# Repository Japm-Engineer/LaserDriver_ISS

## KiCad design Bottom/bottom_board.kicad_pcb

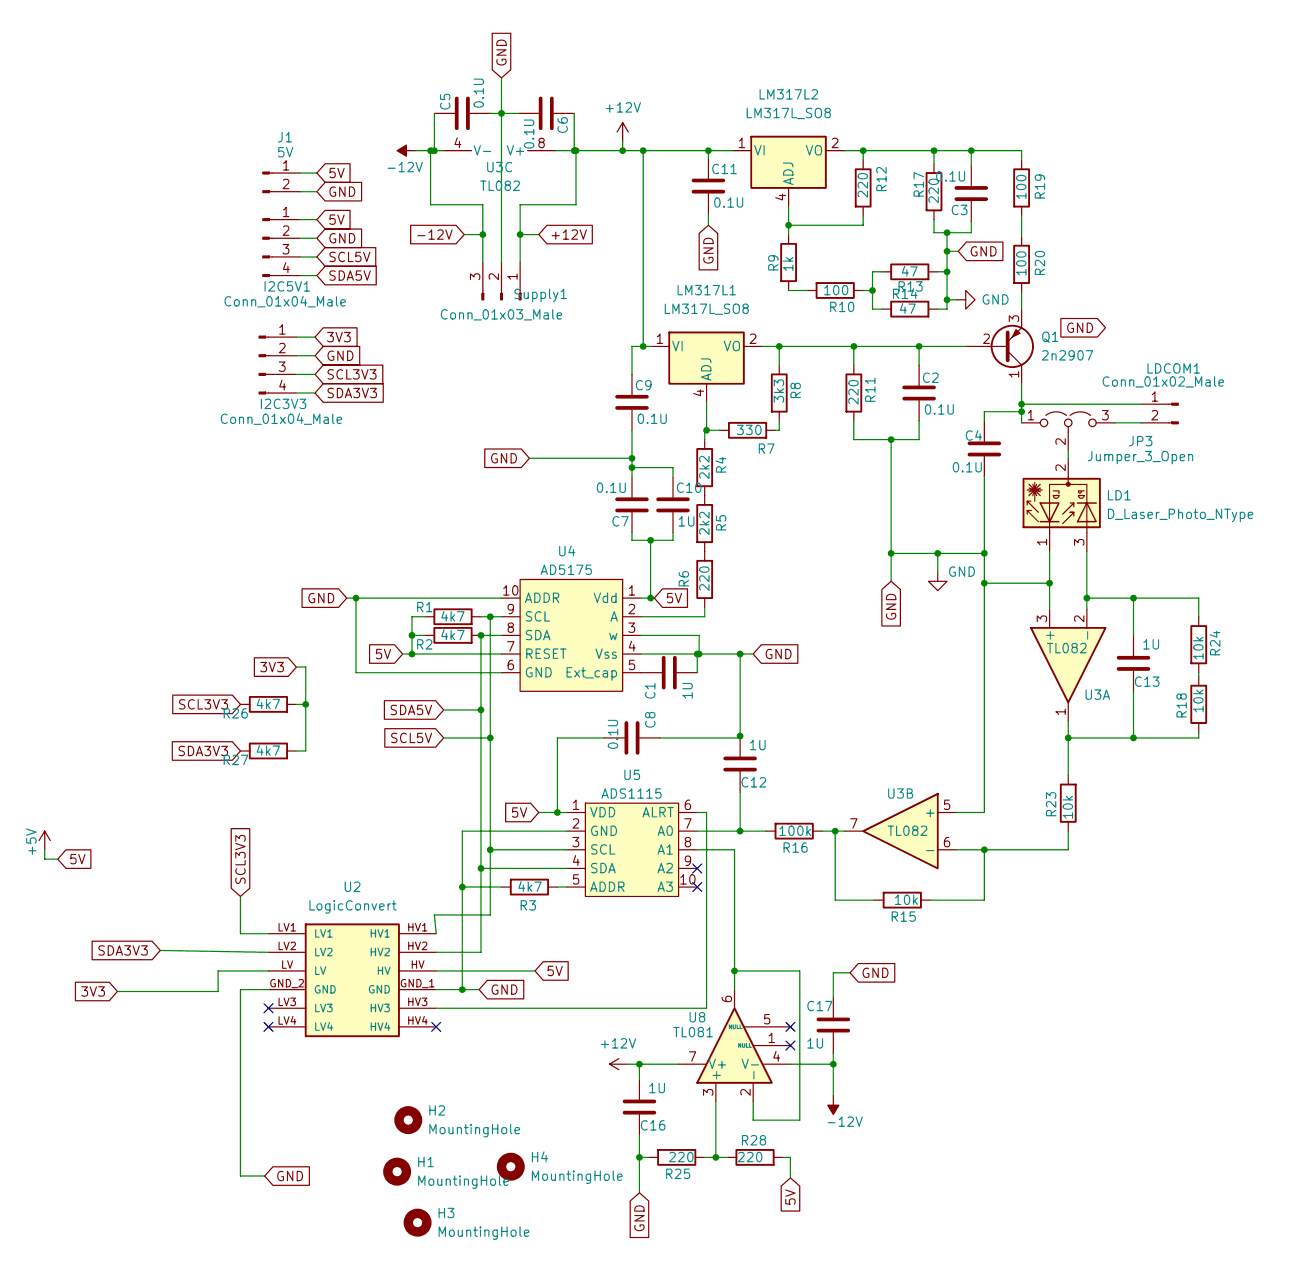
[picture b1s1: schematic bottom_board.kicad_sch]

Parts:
C1, C10, C12, C13, C16, C17: 1U; C_0805_2012Metric_Pad1.18x1.45mm_HandSolder
C2, C3, C4, C5, C6, C7, C8, C9, C11: 0.1U; C_0805_2012Metric_Pad1.18x1.45mm_HandSolder
H1, H2, H3, H4: MountingHole; MountingHole_3.2mm_M3
I2C3V3, I2C5V1: Conn_01x04_Male; JST_XA_B04B-XASK-1_1x04_P2.50mm_Vertical
J1: 5V; JST_EH_B2B-EH-A_1x02_P2.50mm_Vertical
JP3: Jumper_3_Open; PinHeader_1x03_P2.54mm_Vertical
LD1: D_Laser_Photo_NType; JST_XH_B3B-XH-A_1x03_P2.50mm_Vertical
LDCOM1: Conn_01x02_Male; JST_EH_B2B-EH-A_1x02_P2.50mm_Vertical
LM317L1, LM317L2: LM317L_SO8; SO-8_3.9x4.9mm_P1.27mm
Q1: 2n2907; TO-92_Inline_Wide
R1, R2, R3, R26, R27: 4k7; R_1210_3225Metric_Pad1.30x2.65mm_HandSolder
R4, R5: 2k2; R_1210_3225Metric_Pad1.30x2.65mm_HandSolder
R6, R12, R25, R28: 220; R_1210_3225Metric_Pad1.30x2.65mm_HandSolder
R7: 330; R_1210_3225Metric_Pad1.30x2.65mm_HandSolder
R8: 3k3; R_1210_3225Metric_Pad1.30x2.65mm_HandSolder
R9: 1k; R_1210_3225Metric_Pad1.30x2.65mm_HandSolder
R10: 100; R_1210_3225Metric_Pad1.30x2.65mm_HandSolder
R11, R17: 220; R_Axial_DIN0614_L14.3mm_D5.7mm_P20.32mm_Horizontal
R13, R14: 47; R_1210_3225Metric_Pad1.30x2.65mm_HandSolder
R15, R18, R23, R24: 10k; R_1210_3225Metric_Pad1.30x2.65mm_HandSolder
R16: 100k; R_1210_3225Metric_Pad1.30x2.65mm_HandSolder
R19, R20: 100; R_Axial_DIN0614_L14.3mm_D5.7mm_P20.32mm_Horizontal
Supply1: Conn_01x03_Male; JST_XH_B3B-XH-A_1x03_P2.50mm_Vertical
U2: LogicConvert; CONV_BOB-12009; PARTREV 01
U3: TL082; SO-8_5.3x6.2mm_P1.27mm
U4: AD5175; MSOP-10_3x3mm_P0.5mm
U5: ADS1115
U8: TL081; DIP-8_W7.62mm

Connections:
3V3: I2C3V3.1, R26.2, R27.2, U2.LV
5V: C7.1, C8.2, C10.2, I2C5V1.1, J1.1, R1.1, R2.1, R28.2, U2.HV, U4.1 (Vdd), U4.7 (RESET), U5.1 (VDD)
+12V: C6.1, C9.1, C11.1, C16.2, LM317L1.1 (VI), LM317L2.1 (VI), Supply1.1, U3.8 (V+), U8.7 (V+)
-12V: C5.1, C17.2, Supply1.3, U3.4 (V-), U8.4 (V-)
GND: C1.2, C2.2, C3.1, C4.2, C5.2, C6.2, C7.2, C8.1, C9.2, C10.1, C11.2, C12.2, C16.1, C17.1, I2C3V3.2, I2C5V1.2, J1.2, LD1.1, R3.2, R11.2, R13.2, R14.2, R17.2, R25.2, Supply1.2, U2.GND_1 (GND), U2.GND_2 (GND), U3.3 (+), U3.5 (+), U4.3 (w), U4.4 (Vss), U4.6 (GND), U4.10 (ADDR), U5.2 (GND)
unnamed: C3.2, LM317L2.2 (VO), LM317L2.3 (VO), LM317L2.6 (VO), LM317L2.7 (VO), R12.1, R17.1, R19.1
unnamed: C13.1, R18.1, R23.2, U3.1
unnamed: C4.1, JP3.1 (A), LDCOM1.1, Q1.1 (C)
unnamed: JP3.3 (B), LDCOM1.2
unnamed: JP3.2 (C), LD1.2
unnamed: LM317L1.4 (ADJ), R4.1, R7.1
unnamed: LM317L2.4 (ADJ), R9.1, R12.2
unnamed: C2.1, LM317L1.2 (VO), LM317L1.3 (VO), LM317L1.6 (VO), LM317L1.7 (VO), Q1.2 (B), R8.1, R11.1
unnamed: Q1.3 (E), R20.2
unnamed: R4.2, R5.1
unnamed: R5.2, R6.2
unnamed: R7.2, R8.2
unnamed: R10.1, R13.1, R14.1
unnamed: R9.2, R10.2
unnamed: R15.2, R16.1, U3.7
unnamed: R18.2, R24.2
unnamed: R19.2, R20.1
unnamed: C13.2, LD1.3, R24.1, U3.2 (-)
unnamed: R15.1, R23.1, U3.6 (-)
unnamed: R6.1, U4.2 (A)
unnamed: C1.1, U4.5 (Ext_cap)
unnamed: C12.1, R16.2, U5.7 (A0)
unnamed: U5.8 (A1), U8.2 (-), U8.6
unnamed: R3.1, U5.5 (ADDR)
unnamed: U2.HV3, U5.6 (ALRT)
unnamed: R25.1, R28.1, U8.3 (+)
SCL3V3: I2C3V3.3, R26.1, U2.LV1
SCL5V: I2C5V1.3, R1.2, U2.HV1, U4.9 (SCL), U5.3 (SCL)
SDA3V3: I2C3V3.4, R27.1, U2.LV2
SDA5V: I2C5V1.4, R2.2, U2.HV2, U4.8 (SDA), U5.4 (SDA)

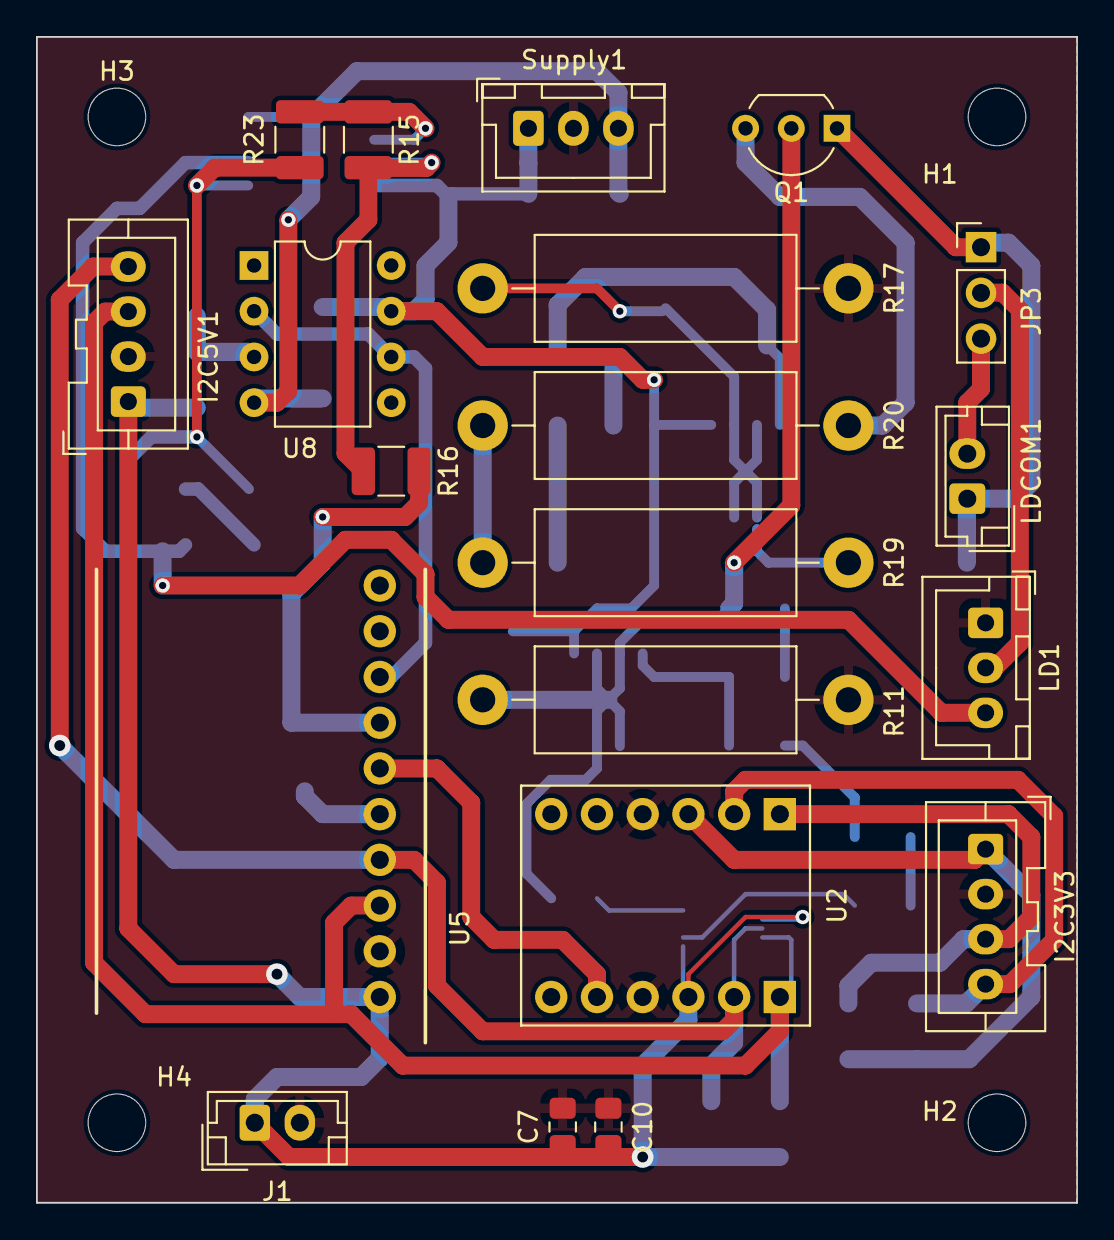
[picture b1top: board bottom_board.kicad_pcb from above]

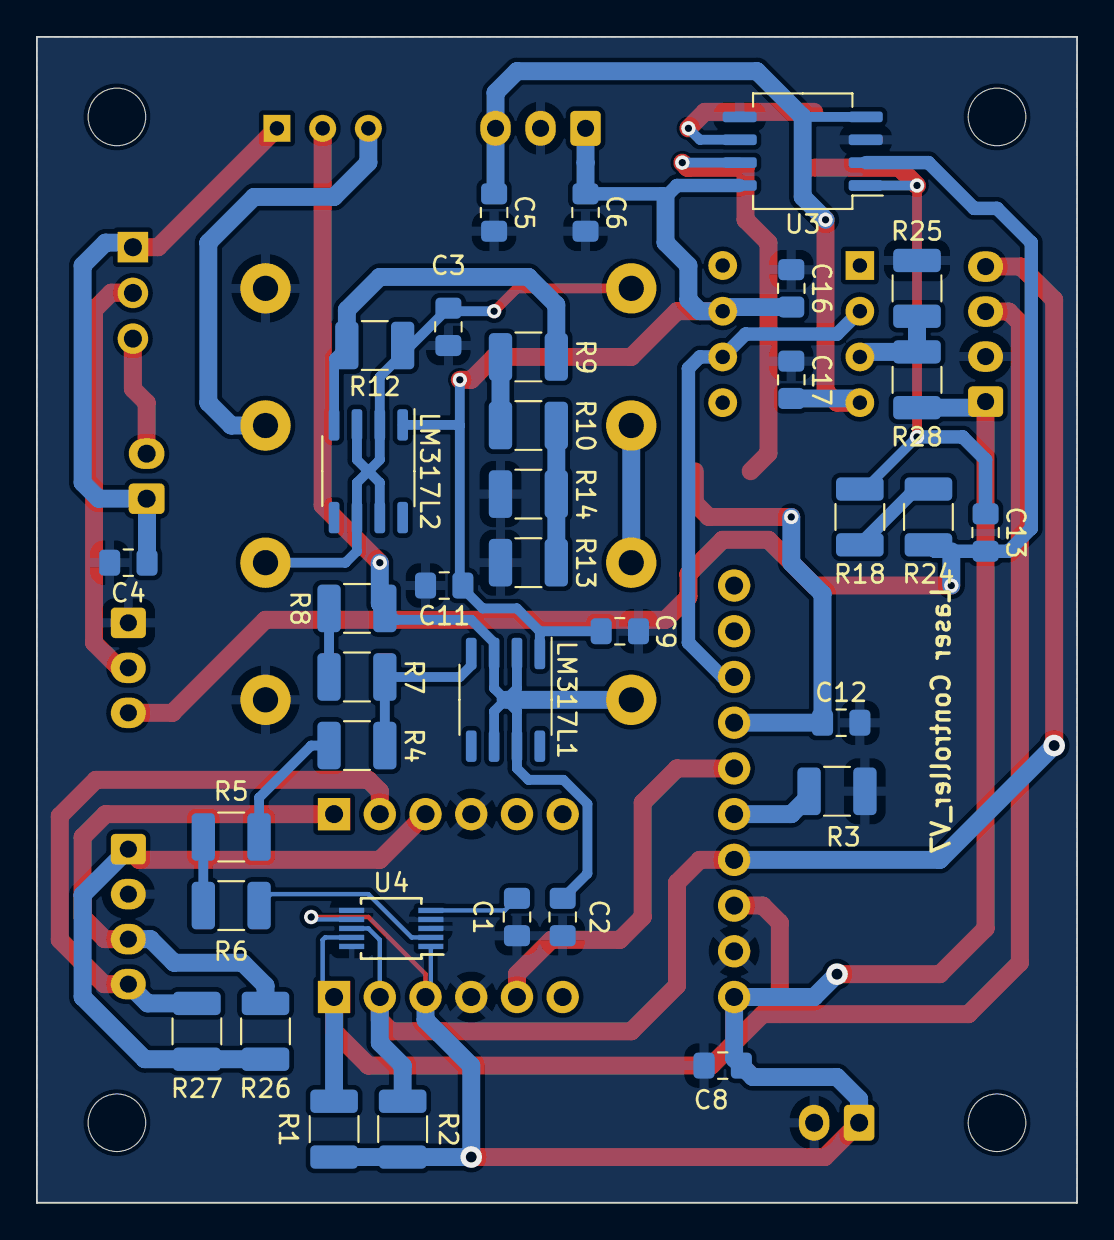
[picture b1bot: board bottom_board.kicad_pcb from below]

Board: 2 copper layers, 57.8 x 64.8 mm, 60 parts (36 on the bottom side), 35 nets.

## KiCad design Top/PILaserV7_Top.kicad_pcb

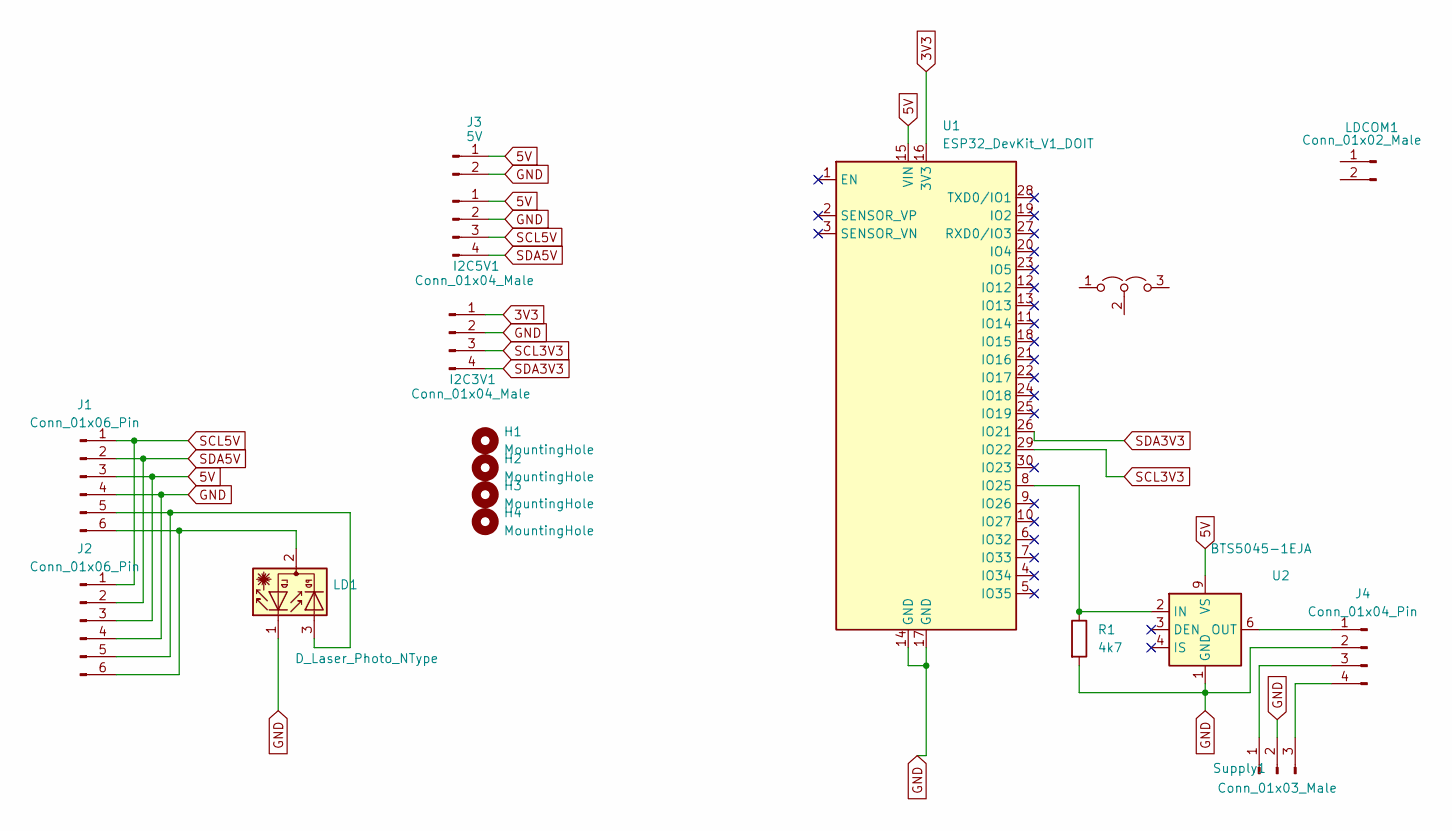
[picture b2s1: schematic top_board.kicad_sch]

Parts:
H1, H2, H3, H4: MountingHole; MountingHole_3.2mm_M3
I2C3V1, I2C5V1: Conn_01x04_Male; JST_XA_B04B-XASK-1_1x04_P2.50mm_Vertical
J1: Conn_01x06_Pin; PinHeader_1x06_P2.54mm_Vertical
J2: Conn_01x06_Pin; Molex_Pico-Lock_504050-0691_1x06-1MP_P1.50mm_Horizontal
J3: 5V; JST_EH_B2B-EH-A_1x02_P2.50mm_Vertical
J4: Conn_01x04_Pin; Molex_Pico-Lock_504050-0491_1x04-1MP_P1.50mm_Horizontal
JP1: Jumper_3_Open; PinHeader_1x03_P2.54mm_Vertical
LD1: D_Laser_Photo_NType; JST_XH_B3B-XH-A_1x03_P2.50mm_Vertical
LDCOM1: Conn_01x02_Male; JST_EH_B2B-EH-A_1x02_P2.50mm_Vertical
R1: 4k7; R_0805_2012Metric_Pad1.20x1.40mm_HandSolder
Supply1: Conn_01x03_Male; JST_XH_B3B-XH-A_1x03_P2.50mm_Vertical
U1: ESP32_DevKit_V1_DOIT; esp32_devkit_v1_doit
U2: BTS5045-1EJA; Infineon_PG-DSO-8-43

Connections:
3V3: I2C3V1.1, U1.16 (3V3)
5V: I2C5V1.1, J1.3, J2.3, J3.1, U1.15 (VIN), U2.9 (VS)
GND: I2C3V1.2, I2C5V1.2, J1.4, J2.4, J3.2, J4.2, LD1.1, R1.2, Supply1.2, U1.14 (GND), U1.17 (GND), U2.1 (GND)
unnamed: J1.5, J2.5, LD1.3
unnamed: J1.6, J2.6, LD1.2
unnamed: J4.1, U2.6 (OUT), U2.7 (OUT), U2.8 (OUT)
unnamed: J4.3, Supply1.1
unnamed: J4.4, Supply1.3
unnamed: R1.1, U1.8 (IO25), U2.2 (IN)
SCL3V3: I2C3V1.3, U1.29 (IO22)
SCL5V: I2C5V1.3, J1.1, J2.1
SDA3V3: I2C3V1.4, U1.26 (IO21)
SDA5V: I2C5V1.4, J1.2, J2.2

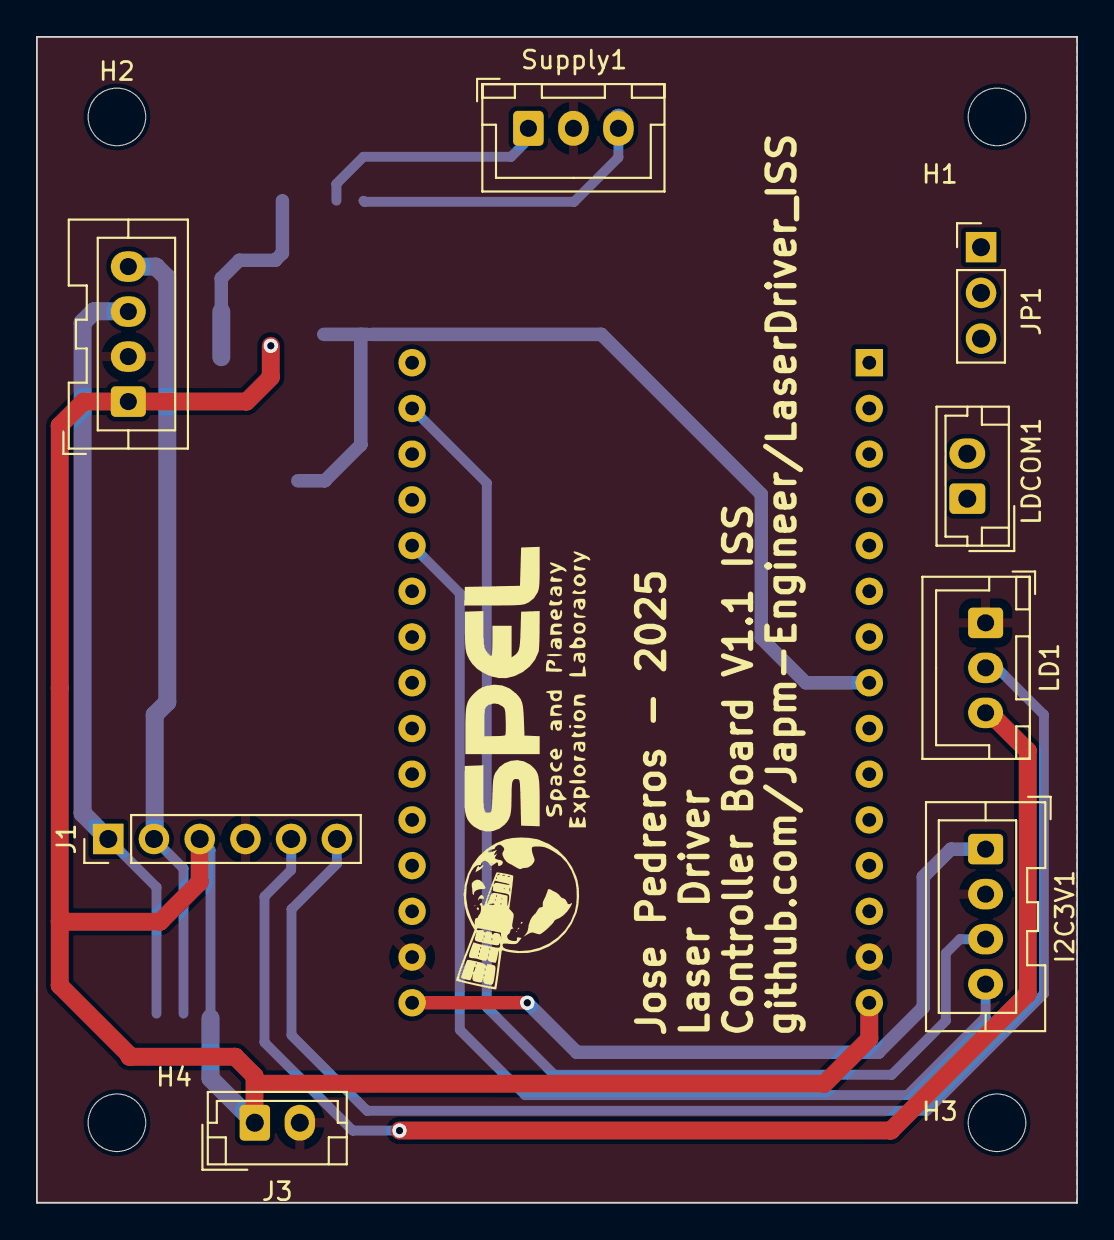
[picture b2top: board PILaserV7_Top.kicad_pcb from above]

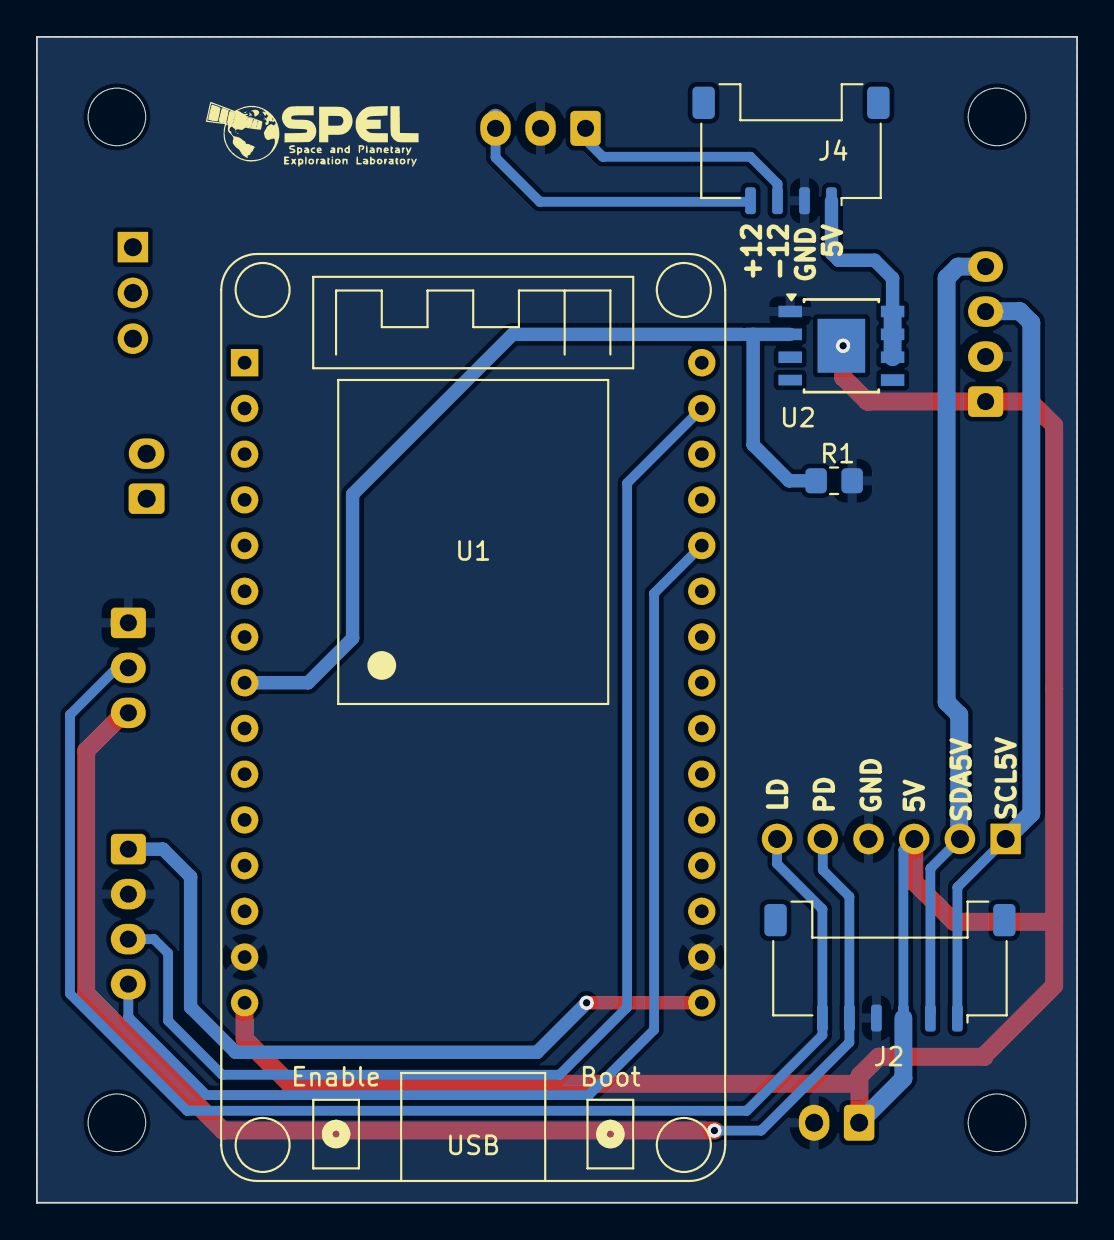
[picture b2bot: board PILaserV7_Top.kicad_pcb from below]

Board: 2 copper layers, 57.8 x 64.8 mm, 17 parts (5 on the bottom side), 13 nets.

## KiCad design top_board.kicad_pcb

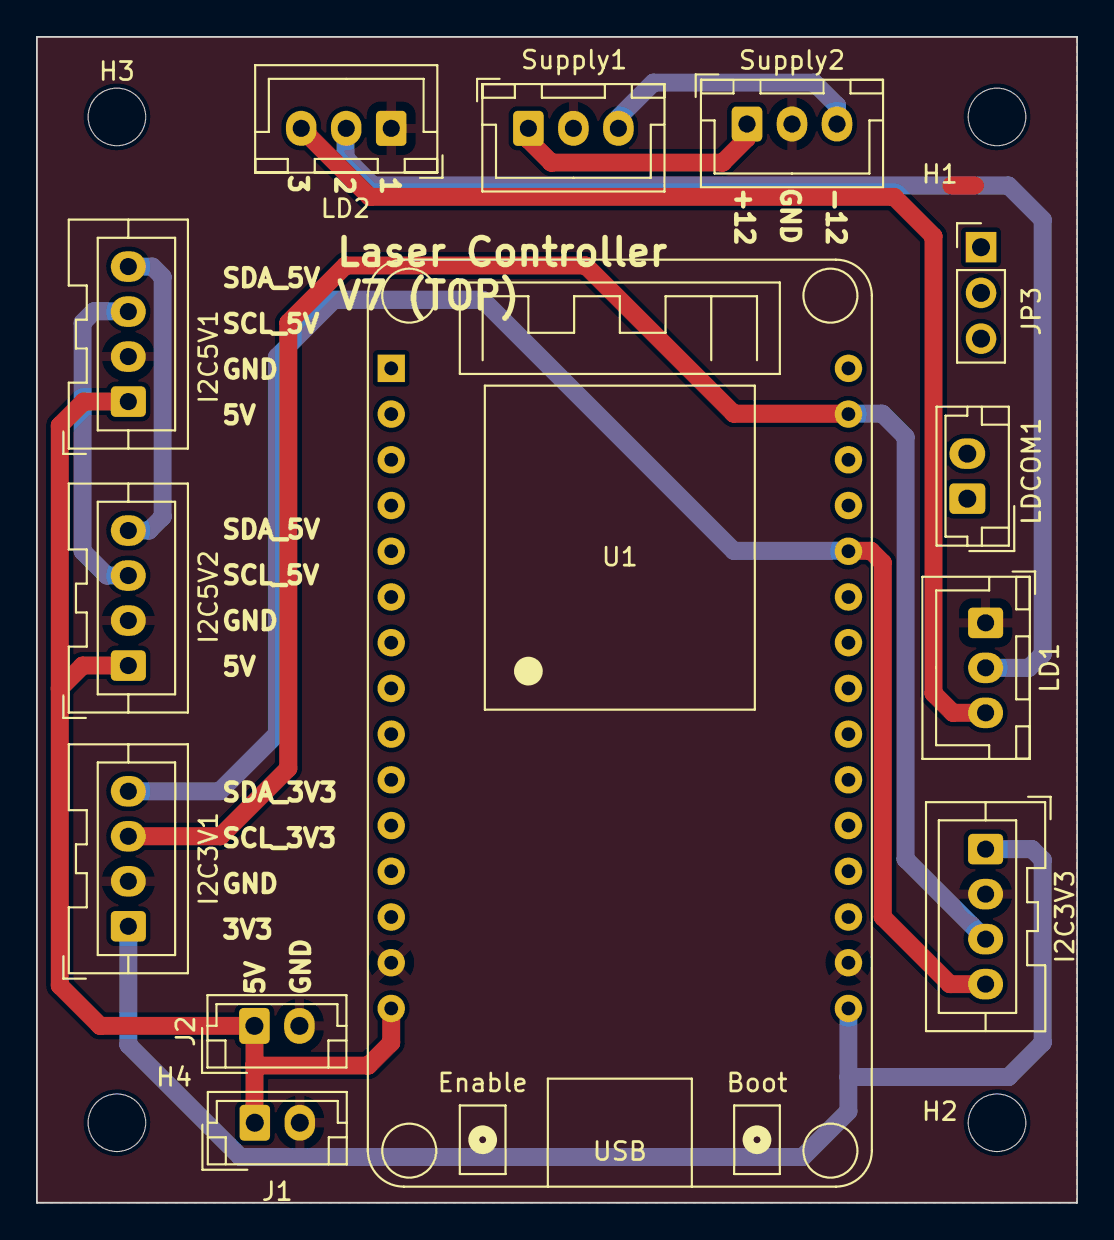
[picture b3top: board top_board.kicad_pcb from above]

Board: 2 copper layers, 57.8 x 64.8 mm, 17 parts (0 on the bottom side), 11 nets.

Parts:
H1, H2, H3, H4: MountingHole; MountingHole_3.2mm_M3
I2C3V1, I2C3V3, I2C5V1, I2C5V2: Conn_01x04_Male; JST_XA_B04B-XASK-1_1x04_P2.50mm_Vertical
J1, J2: 5V; JST_EH_B2B-EH-A_1x02_P2.50mm_Vertical
JP3: Jumper_3_Open; PinHeader_1x03_P2.54mm_Vertical
LD1, LD2: D_Laser_Photo_NType; JST_XH_B3B-XH-A_1x03_P2.50mm_Vertical
LDCOM1: Conn_01x02_Male; JST_EH_B2B-EH-A_1x02_P2.50mm_Vertical
Supply1, Supply2: Conn_01x03_Male; JST_XH_B3B-XH-A_1x03_P2.50mm_Vertical
U1: ESP32_DevKit_V1_DOIT; esp32_devkit_v1_doit

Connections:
3V3: I2C3V1.1, I2C3V3.1, U1.16 (3V3)
5V: I2C5V1.1, I2C5V2.1, J1.1, J2.1, U1.15 (VIN)
GND: I2C3V1.2, I2C3V3.2, I2C5V1.2, I2C5V2.2, J1.2, J2.2, LD1.1, LD2.1, Supply1.2, Supply2.2, U1.14 (GND), U1.17 (GND)
unnamed: LD1.2, LD2.2
unnamed: LD1.3, LD2.3
unnamed: Supply1.1, Supply2.1
unnamed: Supply1.3, Supply2.3
SCL3V3: I2C3V1.3, I2C3V3.3, U1.29 (IO22)
SCL5V: I2C5V1.3, I2C5V2.3
SDA3V3: I2C3V1.4, I2C3V3.4, U1.26 (IO21)
SDA5V: I2C5V1.4, I2C5V2.4

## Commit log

2024-11-18 primera subida
2024-11-18 subida esquematicos
2024-11-18 arreglo
2024-11-19 adding supply
2025-06-18 actualizacion de placa y libreria para versio 1.1
2025-06-18 Logos Agregados
2025-06-18 agregando carpetas y archivos
2025-06-18 agregando carpetas y archivos otra vez
2025-06-18 actualizando gerbers
